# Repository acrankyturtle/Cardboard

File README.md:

# Cardboard

Programmable keyboard controller system with host software, configuration UI, and embedded firmware.

## Architecture Overview

Cardboard is a three-tier system: a **React frontend** for configuration, a **.NET backend** for device management and API serving, and **Rust firmware** running on RP2040-based keyboard controllers. The backend discovers devices over USB serial, while the frontend communicates with the backend over HTTP (REST + SSE).

```
Frontend (React/Vite)  →  Backend (.NET/Kestrel)  →  Device (Rust/Embassy)
```

## Prerequisites

- [.NET SDK 10.0+](https://dotnet.microsoft.com/download)
- [Node.js LTS](https://nodejs.org/) + npm
- [Rust nightly](https://rustup.rs/) + `thumbv6m-none-eabi` target
- `elf2uf2-rs` or `probe-rs` (for flashing firmware)
- [Inno Setup 6.2+](https://jrsoftware.org/isinfo.php) (installer builds only)

## Getting Started

### Backend

```bash
dotnet run --project Cardboard.Controller
```

Starts the API server at `http://localhost:7000`. In Development mode, Swagger is available at `/swagger`.

### Frontend

```bash
cd react-frontend
npm install
npm run dev
```

Starts the Vite dev server at `http://localhost:5173`. The `appsettings.Development.json` in `Cardboard.Controller/` points `ReactHostUrl` to `:5173` so the backend knows where the frontend is running.

### Firmware

```bash
cd firmware
cargo build --release
cargo run --release
```

Flashes the firmware to a connected RP2040 device. The default runner uses `elf2uf2-rs` (device must be in bootloader mode). To use `probe-rs`, edit `.cargo/config.toml`.

## Building for Release

### Application

```bash
dotnet publish Cardboard.Controller -c Release
```

This automatically builds the React frontend (`npm install && npm run build`) and bundles it into the output under `wwwroot/`.

### Installer

```powershell
installer\build-installer.ps1
```

Requires Inno Setup 6.2+ installed.

### Firmware

```bash
cd firmware
cargo build --release
```

## Project Structure

### Host Application (C# / .NET 10)

| Project | Purpose |
|---------|---------|
| `Cardboard.Controller/` | ASP.NET Core host, DI composition root, entry point |
| `Cardboard.HttpApi/` | REST API endpoint definitions (Devices, Tags, Logs, InputDevices, Controller) |
| `Cardboard.Api/` | Shared API setup, such as JSON serialization configuration |
| `Cardboard.FrontendHost/` | SPA hosting, origin validation, route mounting |
| `Cardboard.Services/` | Business logic: tag association management, virtual key dispatch |
| `Cardboard.Repositories/` | Data access: device repository, association persistence |
| `Cardboard.Events/` | Cross-platform event abstractions |
| `Cardboard.Device/` | Device abstractions: commands, profiles, settings, binary serialization |
| `Cardboard.Serial/` | Serial port abstractions |
| `Cardboard.Windows/` | Windows: serial discovery (WMI), input monitoring, tray icon |
| `Cardboard.Metadata/` | Device metadata interfaces (icons, model info) |
| `Cardboard.Utilities/` | Shared utilities: AsyncDispatchSubject, Result types, file watcher |
| `Cardboard.Update/` | Firmware update orchestration |
| `Cardboard.Update.Api/` | Update server API client |
| `Cardboard.Update.Api.Abstractions/` | Shared types for update client/server |
| `Cardboard.UpdateServer/` | Firmware, metadata, and update distribution server (separate deployment) |

### Firmware (Rust / Embassy)

| Directory | Purpose |
|-----------|---------|
| `firmware/` | CK1-30 firmware entry point and RP2040-specific code |
| `cardboard-lib/` | Platform-agnostic core: commands, profiles, state machine, HID, serial |

### Frontend (TypeScript / React 19)

| Directory | Purpose |
|-----------|---------|
| `react-frontend/` | Vite + React + Tailwind SPA for device configuration |

### Tooling

| Directory | Purpose |
|-----------|---------|
| `DeviceTool/` | CLI tool for building and testing device profiles |
| `installer/` | Inno Setup installer scripts and build script |

## Configuration

**`Cardboard.Controller/appsettings.json`** — Production configuration:

- `Kestrel:Endpoints:Http:Url` — Backend listen address (default `http://127.0.0.1:7000`)
- `Paths:Associations` — Association storage path (default `%APPDATA%/Cardboard/associations.json`)
- `Paths:MetadataCache` / `IconCache` — Cache directories under `%APPDATA%/Cardboard/cache/`
- `Frontend:ReactHostUrl` — URL where the frontend is served from
- `Update:Url` / `Update:Channel` — Firmware update server and release channel

**`appsettings.Development.json`** — Development overrides:

- Sets `Frontend:ReactHostUrl` to `http://localhost:5173` for the Vite dev server
- Sets `Update:Channel` to `preview`

## Code Formatting

| Language | Tool | Config |
|----------|------|--------|
| C# | CSharpier | `.csharpierrc.json` (tabs, 110 width) |
| TypeScript | Prettier + ESLint | `.prettierrc`, `eslint.config.js` |
| Rust | rustfmt | Default settings |

## Further Documentation

- [Architecture](docs/architecture.md) — System architecture deep-dive, component relationships, data flow
- [API Reference](docs/api-reference.md) — HTTP endpoint reference (REST + SSE)
- [Serial Protocol](docs/serial-protocol.md) — Binary protocol between host and firmware
- [Conventions](docs/conventions.md) — Design patterns, code style, project conventions

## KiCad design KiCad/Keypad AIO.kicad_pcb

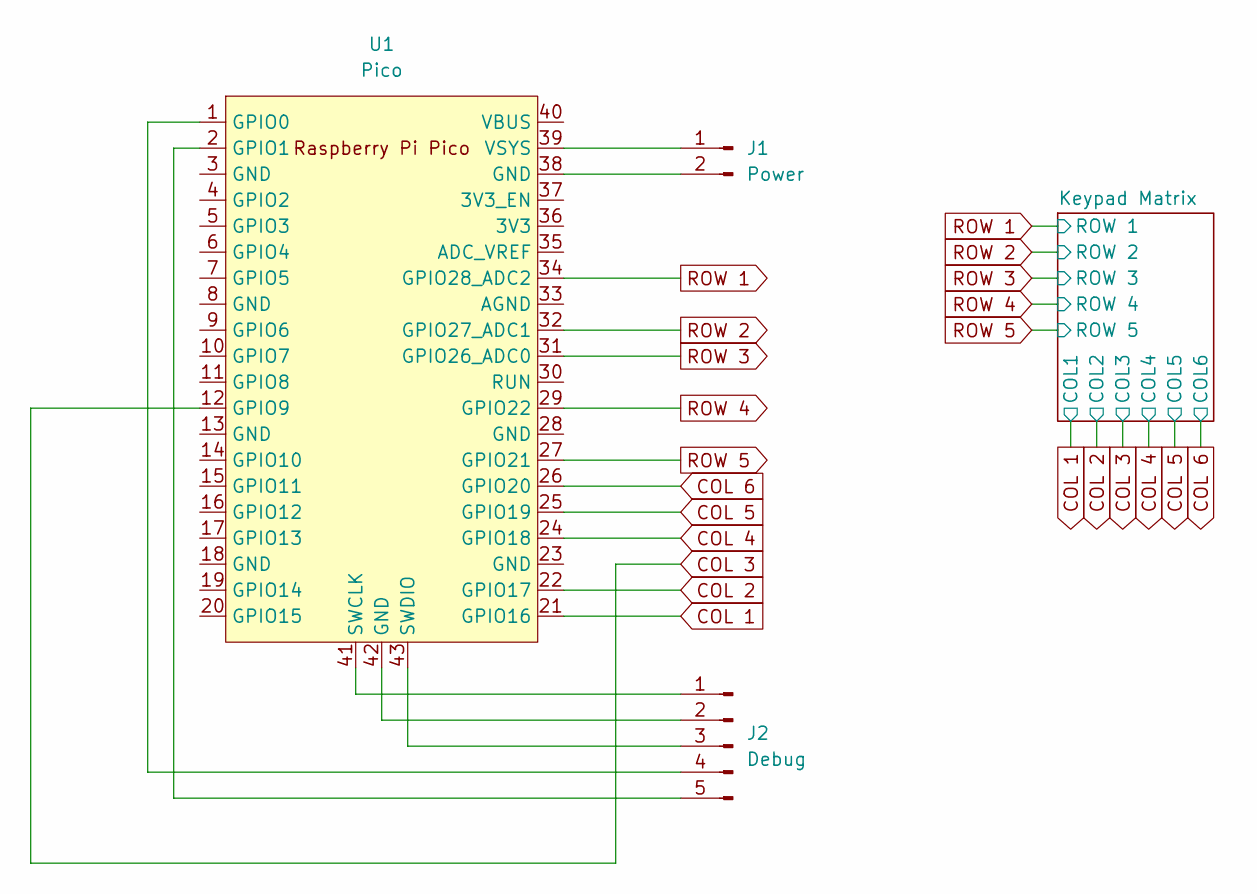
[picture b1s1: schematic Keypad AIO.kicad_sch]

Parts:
J1: Power; JST_XH_S2B-XH-A_1x02_P2.50mm_Horizontal
J2: Debug; JST_XH_B5B-XH-A_1x05_P2.50mm_Vertical
U1: Pico; RPi_Pico_SMD_TH

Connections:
COL 1: U1.21 (GPIO16); also elsewhere on the board
COL 2: U1.22 (GPIO17); also elsewhere on the board
COL 3: U1.12 (GPIO9); also elsewhere on the board
COL 4: U1.24 (GPIO18); also elsewhere on the board
COL 5: U1.25 (GPIO19); also elsewhere on the board
COL 6: U1.26 (GPIO20); also elsewhere on the board
unnamed: J1.1, U1.39 (VSYS)
unnamed: J1.2, U1.38 (GND)
unnamed: J2.1, U1.41 (SWCLK)
unnamed: J2.2, U1.42 (GND)
unnamed: J2.3, U1.43 (SWDIO)
unnamed: J2.4, U1.1 (GPIO0)
unnamed: J2.5, U1.2 (GPIO1)
ROW 1: U1.34 (GPIO28_ADC2); also elsewhere on the board
ROW 2: U1.32 (GPIO27_ADC1); also elsewhere on the board
ROW 3: U1.31 (GPIO26_ADC0); also elsewhere on the board
ROW 4: U1.29 (GPIO22); also elsewhere on the board
ROW 5: U1.27 (GPIO21); also elsewhere on the board

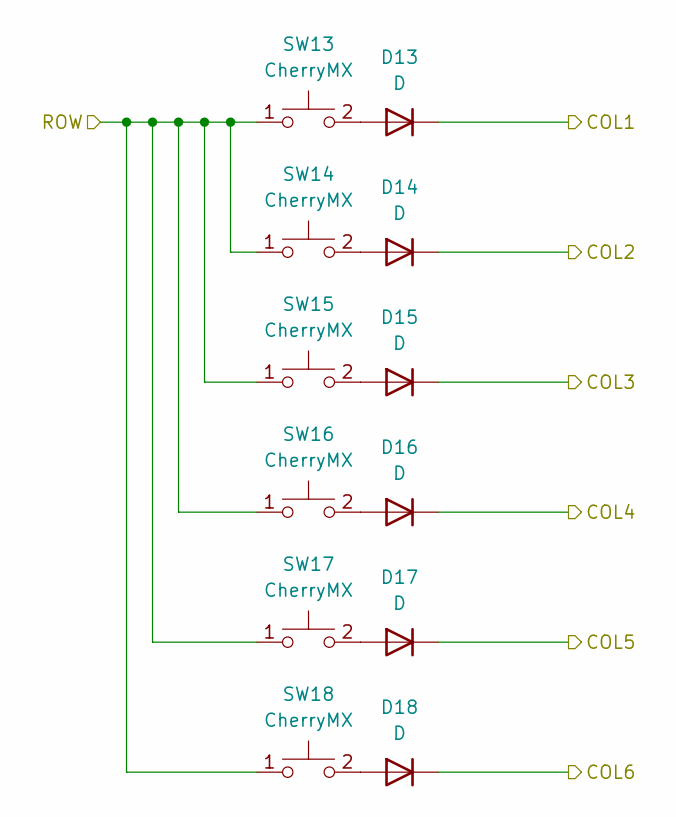
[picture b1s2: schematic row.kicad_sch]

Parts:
D13, D14, D15, D16, D17, D18: D; D_DO-35_SOD27_P7.62mm_Horizontal
SW13, SW14, SW15, SW16, SW17, SW18: CherryMX; SW_Hotswap_Kailh_MX_1.00u

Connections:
COL 1: D13.1 (K); also elsewhere on the board
COL 2: D14.1 (K); also elsewhere on the board
COL 3: D15.1 (K); also elsewhere on the board
COL 4: D16.1 (K); also elsewhere on the board
COL 5: D17.1 (K); also elsewhere on the board
COL 6: D18.1 (K); also elsewhere on the board
unnamed: D13.2 (A), SW13.2
unnamed: D14.2 (A), SW14.2
unnamed: D15.2 (A), SW15.2
unnamed: D16.2 (A), SW16.2
unnamed: D17.2 (A), SW17.2
unnamed: D18.2 (A), SW18.2
ROW 3: SW13.1, SW14.1, SW15.1, SW16.1, SW17.1, SW18.1; also elsewhere on the board

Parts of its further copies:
D1, D2, D3, D4, D5, D6, D7, D8, D9, D10, D11, D12, D19, D20, D21, D22, D23, D24, D25, D26, D27, D28, D29, D30: D; D_DO-35_SOD27_P7.62mm_Horizontal
SW1, SW2, SW3, SW4, SW5, SW6, SW7, SW8, SW9, SW10, SW11, SW12, SW19, SW20, SW21, SW22, SW23, SW24, SW25, SW26, SW27, SW28, SW29, SW30: CherryMX; SW_Hotswap_Kailh_MX_1.00u

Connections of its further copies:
COL 1: D1.1 (K), D7.1 (K), D19.1 (K), D25.1 (K); also elsewhere on the board
COL 2: D2.1 (K), D8.1 (K), D20.1 (K), D26.1 (K); also elsewhere on the board
COL 3: D3.1 (K), D9.1 (K), D21.1 (K), D27.1 (K); also elsewhere on the board
COL 4: D4.1 (K), D10.1 (K), D22.1 (K), D28.1 (K); also elsewhere on the board
COL 5: D5.1 (K), D11.1 (K), D23.1 (K), D29.1 (K); also elsewhere on the board
COL 6: D6.1 (K), D12.1 (K), D24.1 (K), D30.1 (K); also elsewhere on the board
unnamed: D1.2 (A), SW1.2
unnamed: D2.2 (A), SW2.2
unnamed: D3.2 (A), SW3.2
unnamed: D4.2 (A), SW4.2
unnamed: D5.2 (A), SW5.2
unnamed: D6.2 (A), SW6.2
unnamed: D7.2 (A), SW7.2
unnamed: D8.2 (A), SW8.2
unnamed: D9.2 (A), SW9.2
unnamed: D10.2 (A), SW10.2
unnamed: D11.2 (A), SW11.2
unnamed: D12.2 (A), SW12.2
unnamed: D19.2 (A), SW19.2
unnamed: D20.2 (A), SW20.2
unnamed: D21.2 (A), SW21.2
unnamed: D22.2 (A), SW22.2
unnamed: D23.2 (A), SW23.2
unnamed: D24.2 (A), SW24.2
unnamed: D25.2 (A), SW25.2
unnamed: D26.2 (A), SW26.2
unnamed: D27.2 (A), SW27.2
unnamed: D28.2 (A), SW28.2
unnamed: D29.2 (A), SW29.2
unnamed: D30.2 (A), SW30.2
ROW 1: SW1.1, SW2.1, SW3.1, SW4.1, SW5.1, SW6.1; also elsewhere on the board
ROW 2: SW7.1, SW8.1, SW9.1, SW10.1, SW11.1, SW12.1; also elsewhere on the board
ROW 4: SW19.1, SW20.1, SW21.1, SW22.1, SW23.1, SW24.1; also elsewhere on the board
ROW 5: SW25.1, SW26.1, SW27.1, SW28.1, SW29.1, SW30.1; also elsewhere on the board

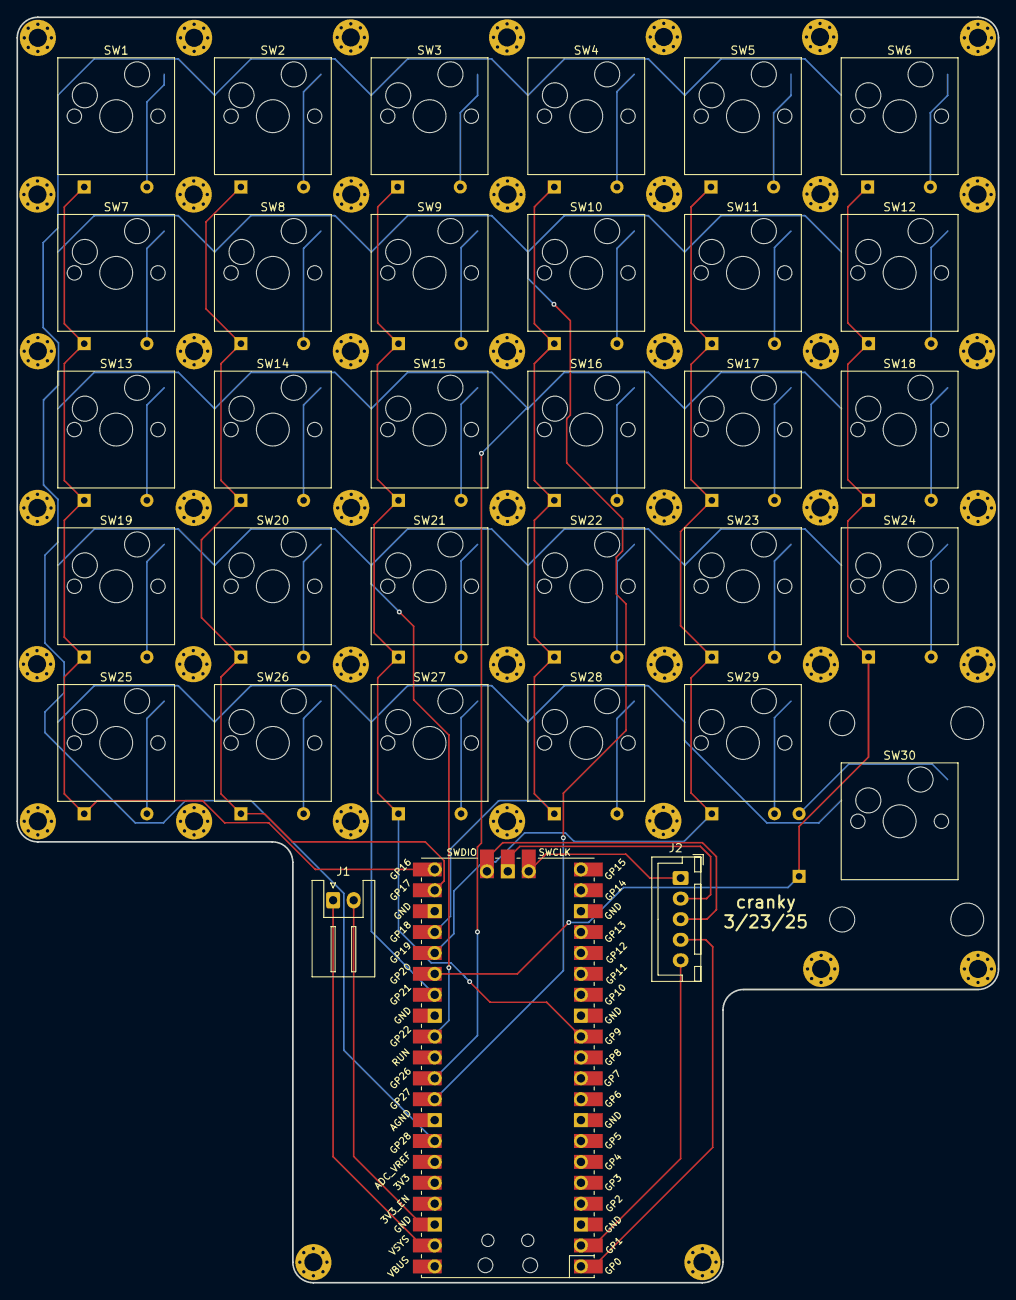
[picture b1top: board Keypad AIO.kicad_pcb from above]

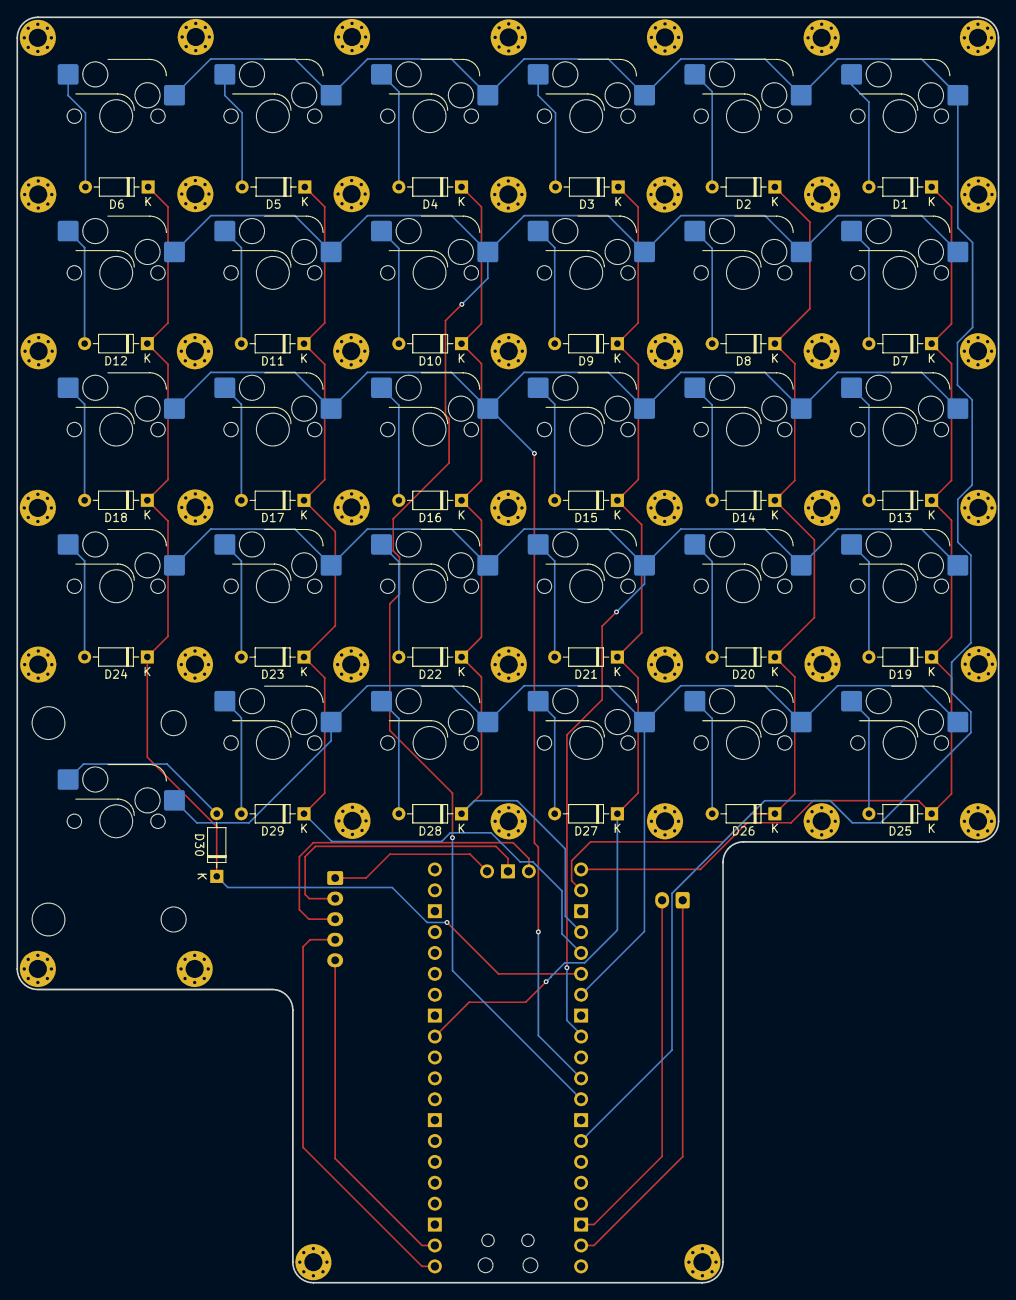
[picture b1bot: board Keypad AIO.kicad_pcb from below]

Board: 2 copper layers, 119.3 x 153.8 mm, 64 parts (30 on the bottom side), 48 nets.

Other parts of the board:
SW30_Stabilizer: Stabilizer_Cherry_MX_2.00u

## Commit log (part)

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2024-06-22 The great renaming
2024-10-14 firmware wip
2024-11-04 serial works i think
2024-11-04 more hmm
2024-11-08 sdgfkj
2024-11-09 commands!
2024-11-24 commands work but flash is fucked
2025-02-15 l8est changes
2025-04-21 before flash memory
2025-05-04 update git ignore
2025-05-04 change profile done
2026-01-02 backend pretty much working
2026-01-02 external tags & frontend started
2026-01-02 lib refactor
2026-01-02 virtual keys implemented
2026-01-02 WIP update runner
2026-01-02 catch all serial exceptions
2026-01-02 WIP frontend
2026-01-02 consolidate windows projects
2026-01-02 windows serial impl fixes and cleanup
2026-01-02 json schemas
2026-01-02 misc logging print cleanup
2026-01-02 frontend good and status stuff added
2026-02-10 updater stuff
2026-02-10 remove untracked cardboard-lib files from gitignore update
2026-02-10 ai cleanup
2026-02-10 minor device tool cleanup
2026-02-10 streams, flash partitions, settings, mouse toggle
2026-02-10 firmware readme files
2026-02-10 add device settings report
2026-02-10 csharpier formatting
2026-02-10 edit device settings frontend
2026-02-10 misc cleanup
2026-02-10 frontend hosting
2026-02-10 put action in edit mode on insert
2026-02-10 git ignore for cardboard-lib
2026-02-10 perf: less allocations when ticking state
2026-02-10 reboot command
2026-02-10 add log view
2026-02-10 device tool can upload settings
2026-02-10 perf: initial running macro vec has capacity of 8
2026-02-10 fix tray icon right click windows bug
2026-02-10 scroll action into view when inserting or editing
2026-02-10 list input devices api
2026-02-10 server events for devices being connected and disconnected
2026-02-10 no space after icon in device card
2026-02-10 dashboard page
2026-02-10 macro templates
2026-02-10 server side device connection event uses keepalive
2026-02-10 profile name can be edited
2026-02-10 memoize change tracking
2026-02-10 fix device matching
2026-02-10 button has ref prop
2026-02-10 fix frontend url appsetting
2026-02-10 installer
2026-02-10 macro channel editing support
2026-02-10 application icon
2026-02-10 associations editor
2026-02-10 deduplicate remove icon
2026-02-10 reduce header flicker on loading profile and settings
2026-02-10 abortcontroller in frontend
2026-02-10 remove unnecessary firmware file
2026-02-10 saving profile resets change tracker
2026-02-10 controller update api
2026-02-10 clean up project references
2026-02-10 automatic installer versioning
2026-02-10 timeout for device update reconnection
2026-02-10 file integrity checks for firmware and controller updates
2026-02-10 controller updating in frontend
2026-02-10 redirect url helper
2026-02-10 refactor firmware settings to cardboard lib
2026-02-10 update logging
2026-02-10 csharpier
2026-02-10 firmware variant configuration
2026-02-10 validate version strings and device type ids to prevent traversal attacks
2026-02-10 maybe fix device disconnect bug
2026-02-10 don't show controller console window
2026-02-10 firmware version is {major.minor.patch} and variant is string
2026-02-10 firmware updating is more better
2026-02-10 fix rust warnings
2026-02-10 refactor firmware settings and reboot handling
2026-02-10 backup and restore settings during firmware update
2026-02-10 hardcoded device metadata
2026-02-10 edit association device selector autocomplete is more gooder
2026-02-10 extract web json settings and use in update server
2026-02-10 fix variant not being set by firmware source
2026-02-10 comboinput styles are better
2026-02-10 device type info is per variant
2026-02-10 remove schema project
2026-02-22 get device metadata from update server
2026-02-22 firmware list api
2026-02-22 input component style consistency
2026-02-22 can update devices already in bootloader mode
2026-02-22 use base variant icon if variant doesn't specify one
2026-02-22 deduplicate some action event utils
2026-02-22 remove useEdit hook
2026-02-22 frontend has tooltips
2026-02-22 split device api types into separate files
2026-02-22 fix button style typo
2026-02-22 don't inject JsonSerializerOptions
2026-02-22 extract frontend streaming update logic
2026-02-22 copy/paste and import/export macros
2026-02-22 remove dead frontend code
2026-02-22 metadata types are records
2026-02-22 combine unknown devices from other associations into association device list
2026-02-22 remove private nuget server dependencies
2026-02-22 device icons sourced from update api
2026-02-22 add unknown error to device updater
2026-02-22 allow manual entry of virtual key device ids
2026-02-22 split frontend components into separate files
2026-02-22 api controller and firmware sources use api cache
2026-02-22 remove unused dialog header description prop
2026-02-22 fix equality checks
2026-02-22 remove deprecated WithOpenApi calls
2026-02-22 remove dnd-kit
2026-02-22 api cache
2026-02-22 only show flash bootloader button when device is in bootloader mode
2026-02-22 allow adding of virtual keys when no devices can be found
2026-02-22 remove unused metadata type
2026-02-22 update to .net 10 and update nuget packages
2026-02-22 use strongly typed versions in repositories and api
2026-02-22 simplify update server CORS policy configuration
2026-02-22 clear metadata cache when reinitializing
2026-02-22 remove unused usings in C# projects
2026-02-22 docs
2026-02-22 move update server default paths to config type
2026-02-22 metadata cache uses string enum json converter
2026-02-22 user guides
2026-02-22 seed cache in controller so it can be used without a connection to the update server
2026-02-22 rename EnterBootloader command to Reboot
2026-02-22 help links open tab with no nav bar
2026-02-22 extract context menu icon component
2026-02-22 thick and thin import and export icons
2026-02-22 import/export keys
2026-02-22 frontend has icon
2026-02-22 remove redundant classes in edit macro dialog title
2026-02-22 help link on left side of panel header
2026-02-22 debounce time can be customized
2026-02-22 import/export has more specific file extensions
2026-02-22 key view has context menu
2026-02-22 include allocator capacity in status
2026-02-22 handle task canceled exceptions better in controller api
2026-02-22 frontend formatting
2026-02-22 move import/export key to keys panel
2026-02-22 back button triggers unsaved changes warning
2026-02-22 help links to guide
2026-02-22 color device svg icons
2026-02-22 downsize predelay to u16 from u64
2026-02-22 add action button uses Button component
2026-02-22 device index help button appears to right of flash bootloader device button
2026-02-22 context menus in edit profile
2026-02-22 individual associations can be exported
2026-02-22 rework button styles to better support disabled states
2026-02-22 update api sources are internal for cleaner logging
2026-02-22 default profile has no name
2026-02-22 firmware build script
2026-02-22 remove redundant command test assertion
2026-02-22 fix virtual keys not being initialized
2026-02-22 better display of unnamed devices
2026-02-22 guide page with no nav bar has different page title
2026-02-22 trim empty virtual keys from end of profile when sending to device
2026-02-22 remove unused page component
2026-02-23 clear cache on controller update
2026-02-23 extract profile actions
    better undo/redo descriptions
2026-02-23 autoselect name when creating new macro
2026-02-23 display macros alphabetically
2026-02-23 right click undo/redo to see full list
2026-02-23 macros can be dragged and dropped
2026-02-23 macro dialog autofocuses and can autoselect the name field
2026-02-23 show number of bindings in layer list items
2026-02-23 replace copy/paste macro with duplicate
2026-02-23 tag list editor uses chips
2026-02-23 sortable listbox
2026-02-24 extract isProfileChanged
2026-02-24 layers panel has dnd sorting
2026-02-24 enter accepts dialogs
2026-02-24 button styles are more consistent
2026-02-24 input styles use focus within
2026-02-24 ignore setProfile actions that result in no profile changes
2026-02-24 refactor undo/redo action to support number of items
2026-02-24 extract HeaderBarButton component
2026-02-24 extract chip list input
    match paths use chip list input
2026-02-24 release virtual keys with index beyond bitfield
2026-02-24 don't delete bindings with delete key
2026-02-24 compact action view is separate component
2026-02-24 add binding to macro context menu
2026-02-28 macros can be toggled
2026-02-28 fix spacing on some dialogs
2026-02-28 lost connection overlay
2026-02-28 consolidate some shared icons
    rename XIcon to ThickRemoveIcon
    move CheckIcon to sharedIcons
2026-02-28 update guide for dnd
2026-02-28 input device cache is more concurrency resilient
2026-02-28 extract edit associations dialog
2026-02-28 simplify dnd code
2026-02-28 dnd cancel drag animation doesn't hide original element
2026-02-28 split components out of KeysPanel.tsx
2026-02-28 improve styles for debounce time input
    debounce time input has millisecond preview
    debounce time input uses dark input styles
2026-02-28 dark input style
2026-02-28 action type menu is navigable with arrow keys
2026-02-28 edit macro cut channels uses chip list input
2026-02-28 addBinding profile action checks for duplicate bindings
2026-02-28 deduplicate firmware update dialogs
2026-02-28 refactor devices index
2026-02-28 update select styles
2026-02-28 macro list item shows usage count if not equal to 1
    clean up macro list item styling
2026-02-28 dragged macros are restricted to the window edges
2026-02-28 reorganize component file structure
2026-02-28 remove unused Input component
2026-02-28 escape key clears current input in chip list input
2026-02-28 select first key and macro on edit profile
2026-02-28 button focus styles for data-focus
2026-02-28 api caches seed cache with fallback data marked as stale
2026-02-28 don't log api cache fallback failures if fallback isn't supported
2026-02-28 add kicad project
2026-02-28 fix bad asp.net reference in api project
2026-02-28 fix update server dockerfile
2026-03-01 update installer icon path
2026-03-07 update env vars for update server
2026-03-07 double clicking tray icon opens frontend
2026-03-07 installer targets .net 10.0
2026-03-29 HACK: wait for device to process press and release
    the proper fix is at the device level
2026-05-17 pin rust toolchain version
2026-05-17 remove unused hid traits
2026-05-17 flush empty hid reports on reset
2026-05-17 don't send hid reports if report didn't change
2026-05-19 more detailed 'add binding' name in binding panel
2026-05-19 fix virtual key press+release race at device level
    implements a better fix than the hack in d83064 ("HACK: wait for device to process press and release")
2026-06-07 bump firmware to version 1.0.1
2026-06-07 extract DeviceBuilder to new file
2026-06-07 device tool guid generator is private
2026-06-07 device tool profile builder can be filtered by device type
2026-06-07 device tool profile builder doesn't take device id
2026-06-07 simplify firmware entry point
2026-06-07 rename device tool create keys method for clarity
2026-06-07 add force option to update device api
2026-06-07 edit emblem in frontend
2026-06-07 custom firmware debug endpoint
2026-06-07 deduplicate firmware update endpoints
2026-06-07 add unchecked update device firmware method
2026-06-07 use SendCommandResult instead of tuple
2026-06-07 omit dev appsettings from controller publish
2026-06-07 extract update specific device firmware logic
2026-06-07 rework build controller script to python
    build controller script copies installer to update files
2026-06-07 deduplicate no mouse hid code
2026-06-07 env var for enabling swagger in production
2026-06-07 remove unused firmware update options type
2026-06-07 dialog body has scrollable option to avoid clipping edges
2026-06-07 implement WriteAsync for Vec<u8>
2026-06-07 stamp default settings to flash on initial boot
2026-06-07 settings has version migration
2026-06-08 layer key unit tests
2026-06-08 fix inverted layer key logic
2026-06-08 reload device info after updating
2026-06-08 update device firmware text is yellow
    extract UpdateLink component
2026-06-08 bump controller to version 1.0.1
2026-06-08 bump firmware to version 1.0.2
